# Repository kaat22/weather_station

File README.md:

# Weather Station

## Introduction
The purpose of this project was to make a weather station (Figure 1), which will read and send the measurements to a server.

## Objectives
The basic aim was to make a functional weather station, which would send the data to a server, that could then be read from a computer.
Our secondary aim was to make the weather station rechargeable, using a LiFePO4 battery (Figure 2). Using a battery to power the station allows it to work without being connected to a computer or a power outlet.

## Methods
The microcontroller we used in the project was ESP32-WROOM-32E (Figure 3). The microcontroller has built-in Wi-Fi that allows it to send the data to a server. There are two sensors which measure the temperature, humidity and air pressure.

## Results
We achieved our primary goal of gathering and transferring data (via Wi-Fi) from the station's sensors to a server, wherefrom it can be viewed through a web browser. We also partially achieved our secondary goal of powering the device with a rechargeable battery, however due to an error in the pcb design phase we were unable to get the recharging feature of the charging circuit functional.

## Refrences
ESP-32WROOM-32E datasheet Source:

esp32-wroom-32e_esp32-wroom-32ue_datasheet_en.pdf ([espressif.com](https://www.espressif.com/en/support/documents/technical-documents))

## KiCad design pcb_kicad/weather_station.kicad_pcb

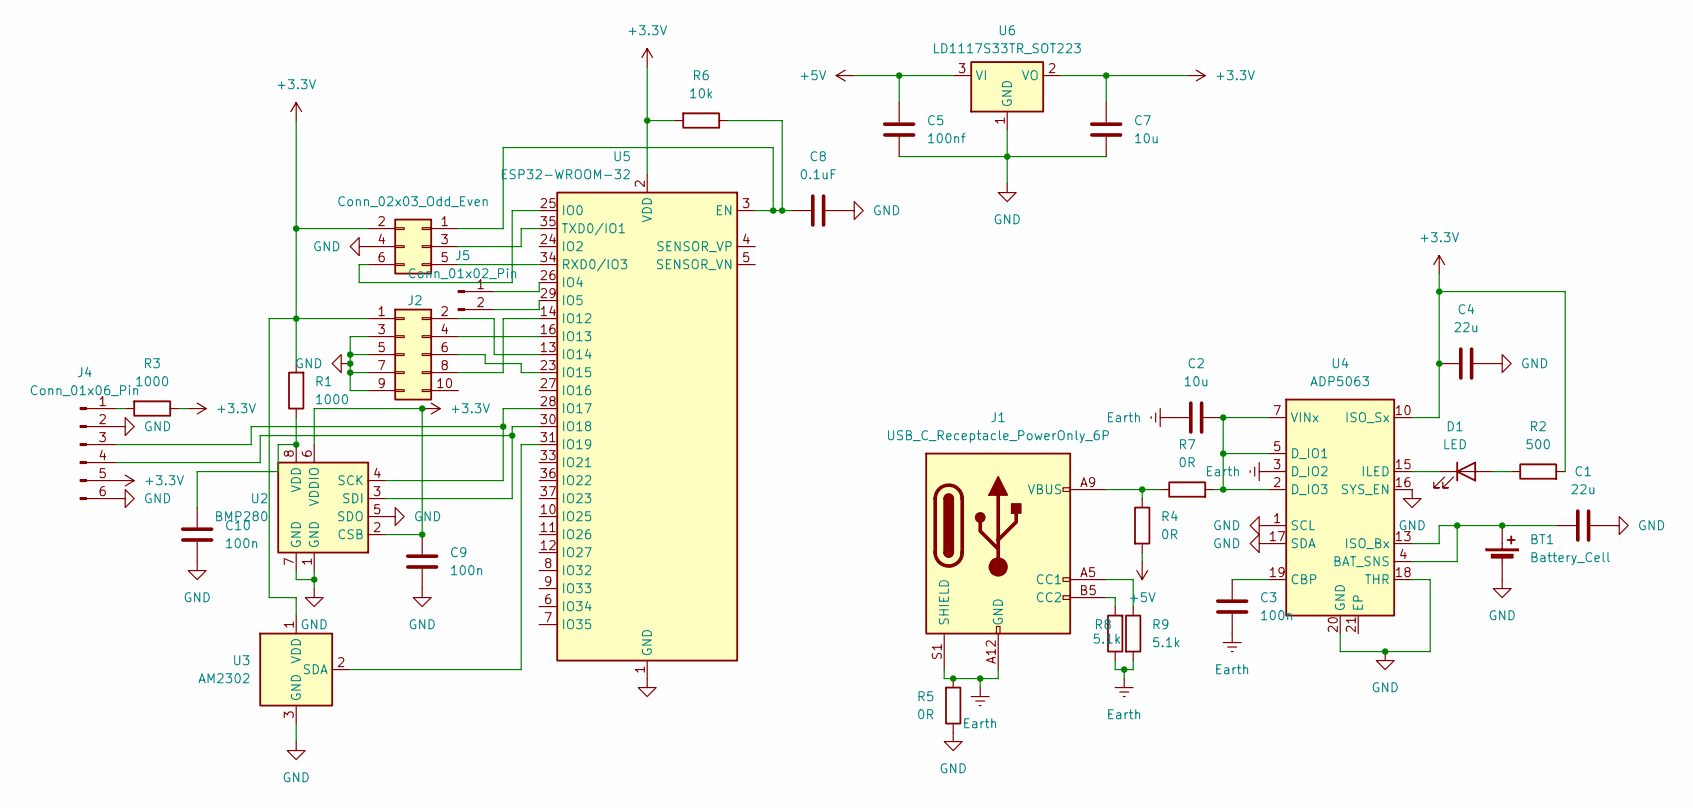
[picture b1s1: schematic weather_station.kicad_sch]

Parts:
BT1: Battery_Cell; BatteryHolder_Keystone_1042_1x18650
C1, C4: 22u; C_0603_1608Metric_Pad1.08x0.95mm_HandSolder
C2, C7: 10u; C_0603_1608Metric_Pad1.08x0.95mm_HandSolder
C3, C9, C10: 100n; C_0603_1608Metric_Pad1.08x0.95mm_HandSolder
C5: 100nf; C_0603_1608Metric_Pad1.08x0.95mm_HandSolder
C8: 0.1uF; C_0603_1608Metric_Pad1.08x0.95mm_HandSolder
D1: LED; LED_0603_1608Metric_Pad1.05x0.95mm_HandSolder
J1: USB_C_Receptacle_PowerOnly_6P; USB_C_Receptacle_GCT_USB4125-xx-x-0190_6P_TopMnt_Horizontal
J2: Conn_02x05_Odd_Even; IDC-Header_2x05_P2.54mm_Vertical
J3: Conn_02x03_Odd_Even; IDC-Header_2x03_P2.54mm_Vertical
J4: Conn_01x06_Pin; PinHeader_1x06_P2.54mm_Vertical
J5: Conn_01x02_Pin; TestPoint_2Pads_Pitch2.54mm_Drill0.8mm
R1, R3: 1000; R_0603_1608Metric_Pad0.98x0.95mm_HandSolder
R2: 500; R_0603_1608Metric_Pad0.98x0.95mm_HandSolder
R4, R5, R7: 0R; R_0603_1608Metric_Pad0.98x0.95mm_HandSolder
R6: 10k; R_0603_1608Metric_Pad0.98x0.95mm_HandSolder
R8, R9: 5.1k; R_0603_1608Metric_Pad0.98x0.95mm_HandSolder
U2: BMP280; Bosch_LGA-8_2.5x2.5mm_P0.65mm_ClockwisePinNumbering
U3: AM2302; ASAIR_AM2302_P2.54mm_Vertical
U4: ADP5063; QFN-20-1EP_4x4mm_P0.5mm_EP2.5x2.5mm
U5: ESP32-WROOM-32; ESP32-WROOM-32D
U6: LD1117S33TR_SOT223; SOT-223-3_TabPin2

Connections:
+3.3V: C4.1, C7.2, C9.1, J2.1, J3.2, J4.5, R1.2, R2.2, R3.1, R6.2, U2.2 (CSB), U2.6 (VDDIO), U3.1 (VDD), U4.9 (ISO_Sx), U4.10 (ISO_Sx), U4.11 (ISO_Sx), U5.2 (VDD), U6.2 (VO); also elsewhere on the board
+5V: C5.1, R4.2, U6.3 (VI)
Earth: C2.2, C3.2, J1.A12 (GND), J1.B12 (GND), J1.S1 (SHIELD), R5.2, R8.1, R9.2, U4.3 (D_IO2)
GND: BT1.2 (-), C1.2, C4.2, C5.2, C7.1, C8.2, C9.2, C10.2, J2.3, J2.5, J2.7, J2.9, J3.4, J4.2, J4.6, R5.1, U2.1 (GND), U2.5 (SDO), U2.7 (GND), U3.3 (GND), U3.4 (GND), U4.1 (SCL), U4.16 (SYS_EN), U4.17 (SDA), U4.18 (THR), U4.20 (GND), U5.1 (GND), U5.15 (GND), U5.38 (GND), U5.39 (GND), U6.1 (GND)
unnamed: D1.2 (A), R2.1
unnamed: D1.1 (K), U4.15 (ILED)
unnamed: J1.A5 (CC1), R9.1
unnamed: J1.B5 (CC2), R8.2
unnamed: J1.A9 (VBUS), J1.B9 (VBUS), R4.1, R7.1
unnamed: J2.2, U5.13 (IO14)
unnamed: J2.4, U5.16 (IO13)
unnamed: J2.6, U5.23 (IO15)
unnamed: J2.8, U5.14 (IO12)
unnamed: C8.1, J3.1, R6.1, U5.3 (EN)
unnamed: J3.3, U5.35 (TXD0/IO1)
unnamed: J3.5, U5.34 (RXD0/IO3)
unnamed: J3.6, U5.25 (IO0)
unnamed: J4.1, R3.2
unnamed: J4.3, U2.4 (SCK), U5.28 (IO17)
unnamed: J4.4, U2.3 (SDI), U5.30 (IO18)
unnamed: J5.1, U5.26 (IO4)
unnamed: J5.2, U5.29 (IO5)
unnamed 22: U5.27 (IO16); also elsewhere on the board
unnamed 23: U5.33 (IO21); also elsewhere on the board
unnamed 24: U5.36 (IO22); also elsewhere on the board
unnamed 25: U5.37 (IO23); also elsewhere on the board
unnamed 26: U5.10 (IO25); also elsewhere on the board
unnamed 27: U5.11 (IO26); also elsewhere on the board
unnamed 28: U5.12 (IO27); also elsewhere on the board
unnamed 29: U5.8 (IO32); also elsewhere on the board
unnamed 30: U5.9 (IO33); also elsewhere on the board
unnamed 31: U5.6 (IO34); also elsewhere on the board
unnamed 32: U5.7 (IO35); also elsewhere on the board
unnamed 33: U5.24 (IO2); also elsewhere on the board
unnamed: C10.1, R1.1, U2.8 (VDD)
unnamed: U3.2 (SDA), U5.31 (IO19)
unnamed: C3.1, U4.19 (CBP)
unnamed: C2.1, R7.2, U4.2 (D_IO3), U4.5 (D_IO1), U4.6 (VINx), U4.7 (VINx), U4.8 (VINx)

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
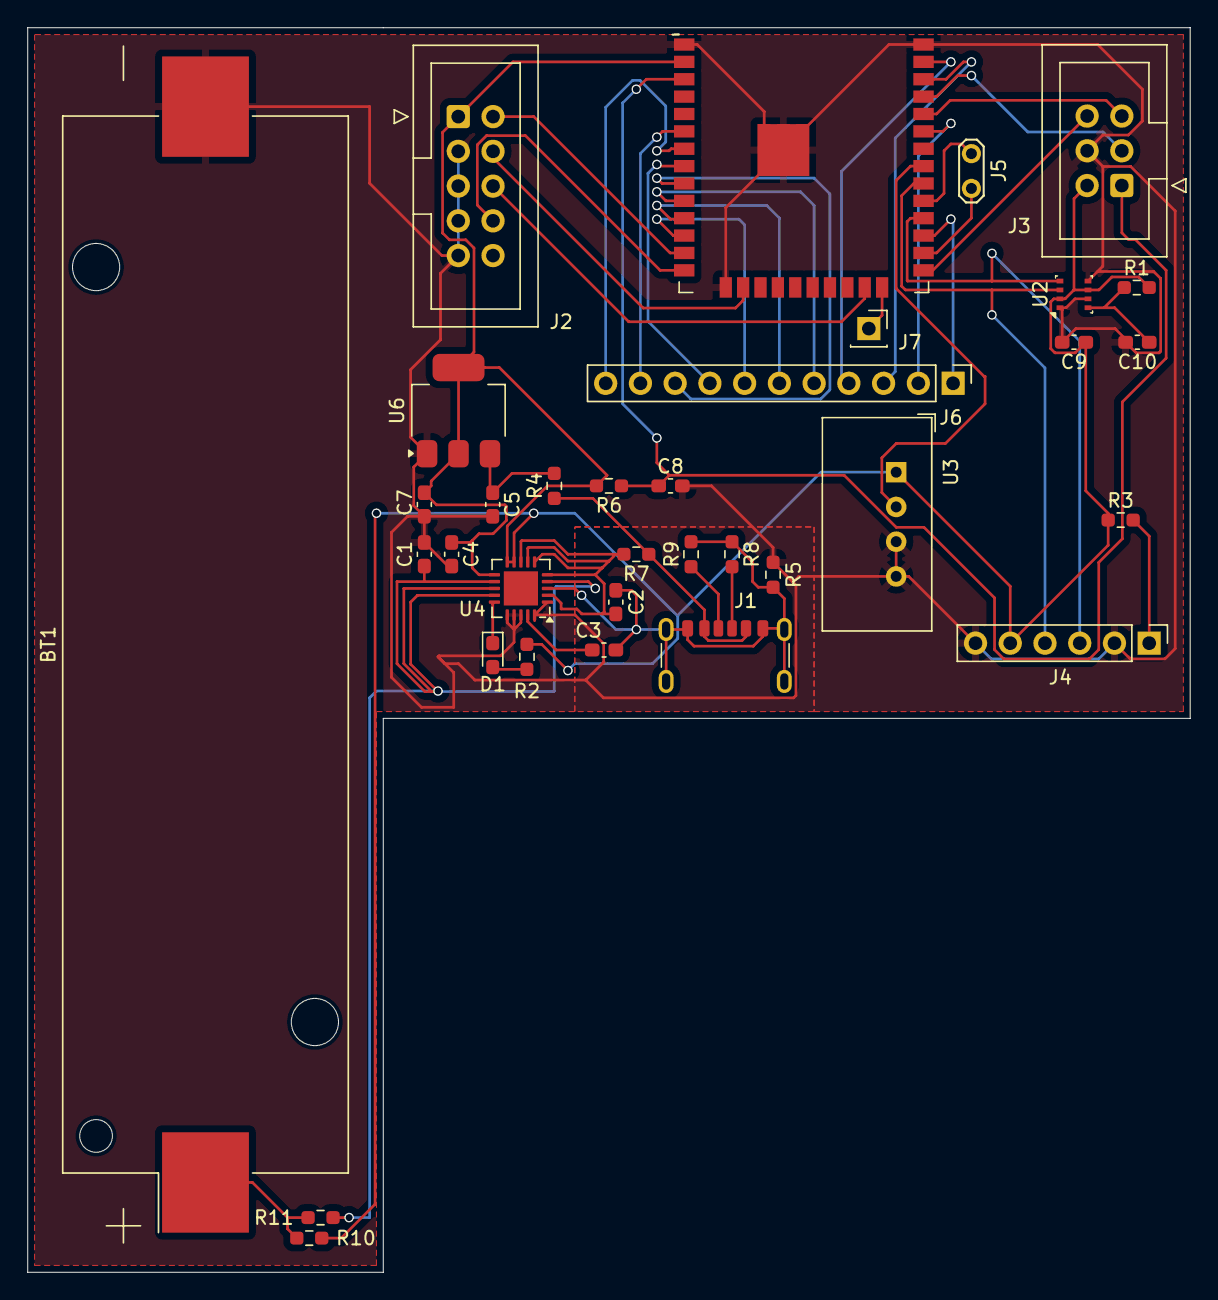
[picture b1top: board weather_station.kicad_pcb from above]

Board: 2 copper layers, 85.0 x 91.0 mm, 34 parts (0 on the bottom side), 40 nets.

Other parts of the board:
J6: Conn_01x11_Pin; PinHeader_1x11_P2.54mm_Vertical
J7: Conn_01x01_Pin; PinSocket_1x01_P2.54mm_Vertical
R10, R11: 0R; R_0603_1608Metric_Pad0.98x0.95mm_HandSolder

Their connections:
+3.3V: R10.2; also elsewhere on the board
unnamed 22: J6.1; also elsewhere on the board
unnamed 23: J6.2; also elsewhere on the board
unnamed 24: J6.3; also elsewhere on the board
unnamed 25: J6.4; also elsewhere on the board
unnamed 26: J6.5; also elsewhere on the board
unnamed 27: J6.6; also elsewhere on the board
unnamed 28: J6.7; also elsewhere on the board
unnamed 29: J6.8; also elsewhere on the board
unnamed 30: J6.9; also elsewhere on the board
unnamed 31: J6.10; also elsewhere on the board
unnamed 32: J6.11; also elsewhere on the board
unnamed 33: J7.1; also elsewhere on the board

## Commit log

2024-03-21 kicad tiedostot
2024-03-21 Added initial circuit diagram
2024-03-21 gitignore
2024-03-21 backuppien poisto
2024-03-25 changed esp32 soc to the esp32wroom
2024-03-26 added voltage regulator circuit for BMP280 VDDIO and and an alternative connection point for BMP280 module
2024-03-27 added full pcb schematic
2024-03-27 added ground fills
2024-03-28 added 0 ohm resistors for battery only mode, out pins for all unused pins from esp 32, opened blind vias and removed unsupported vias and silkscreen drawings from esp32 blueprint
2024-04-05 alustava koodi
2024-04-11 paineen mittauksen lisääminen
2024-04-26 xampp php files
2024-11-19 Update README.md
    Updated the readme with documentation and assets from the from the project poster.
2024-12-04 Update README.md
    typos
